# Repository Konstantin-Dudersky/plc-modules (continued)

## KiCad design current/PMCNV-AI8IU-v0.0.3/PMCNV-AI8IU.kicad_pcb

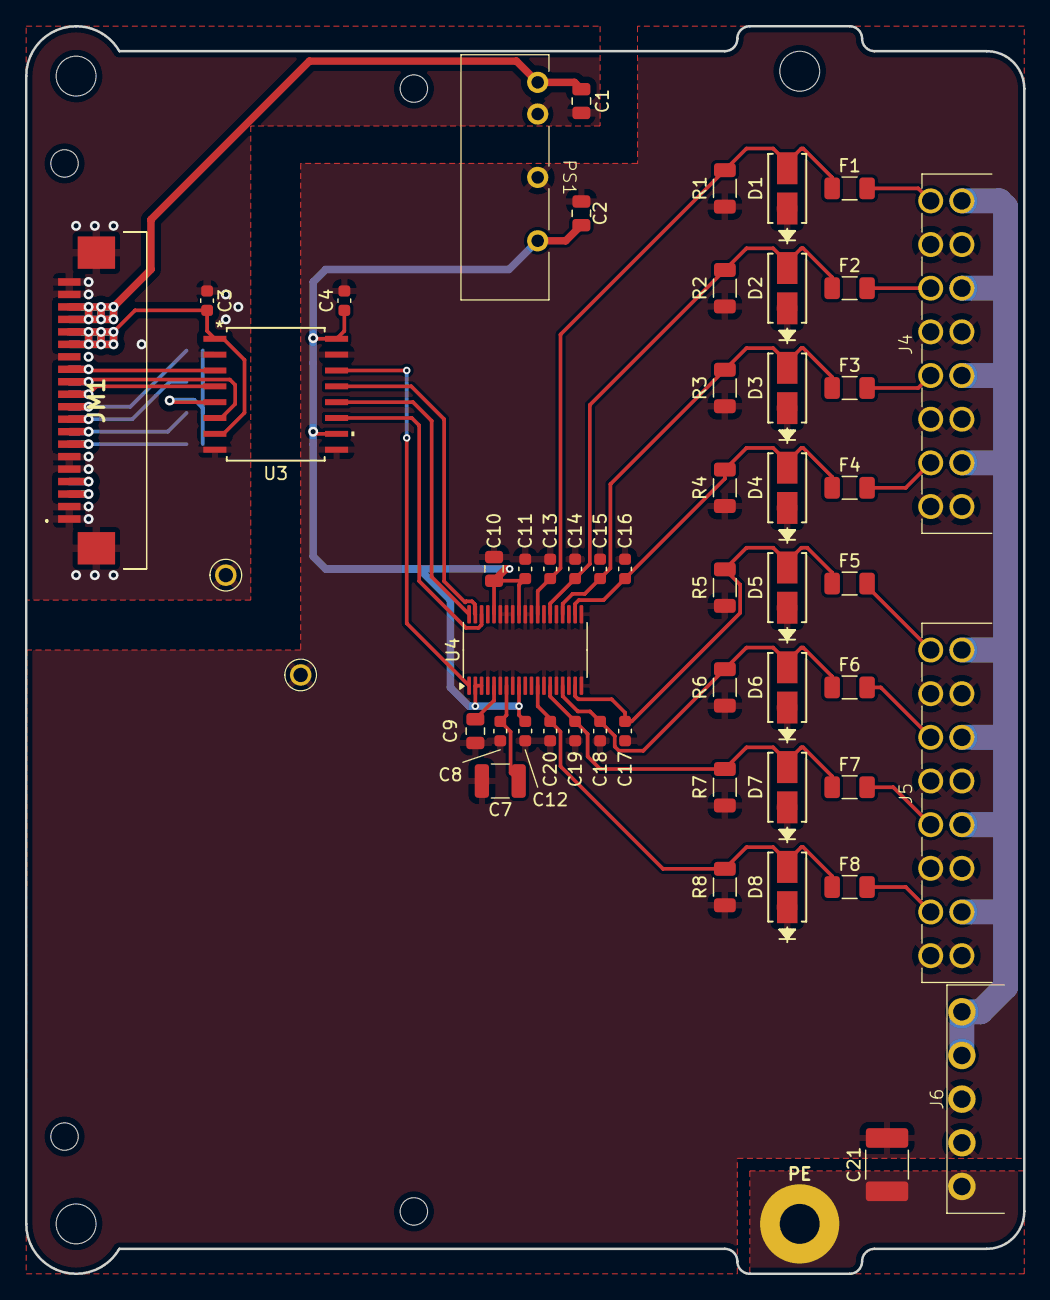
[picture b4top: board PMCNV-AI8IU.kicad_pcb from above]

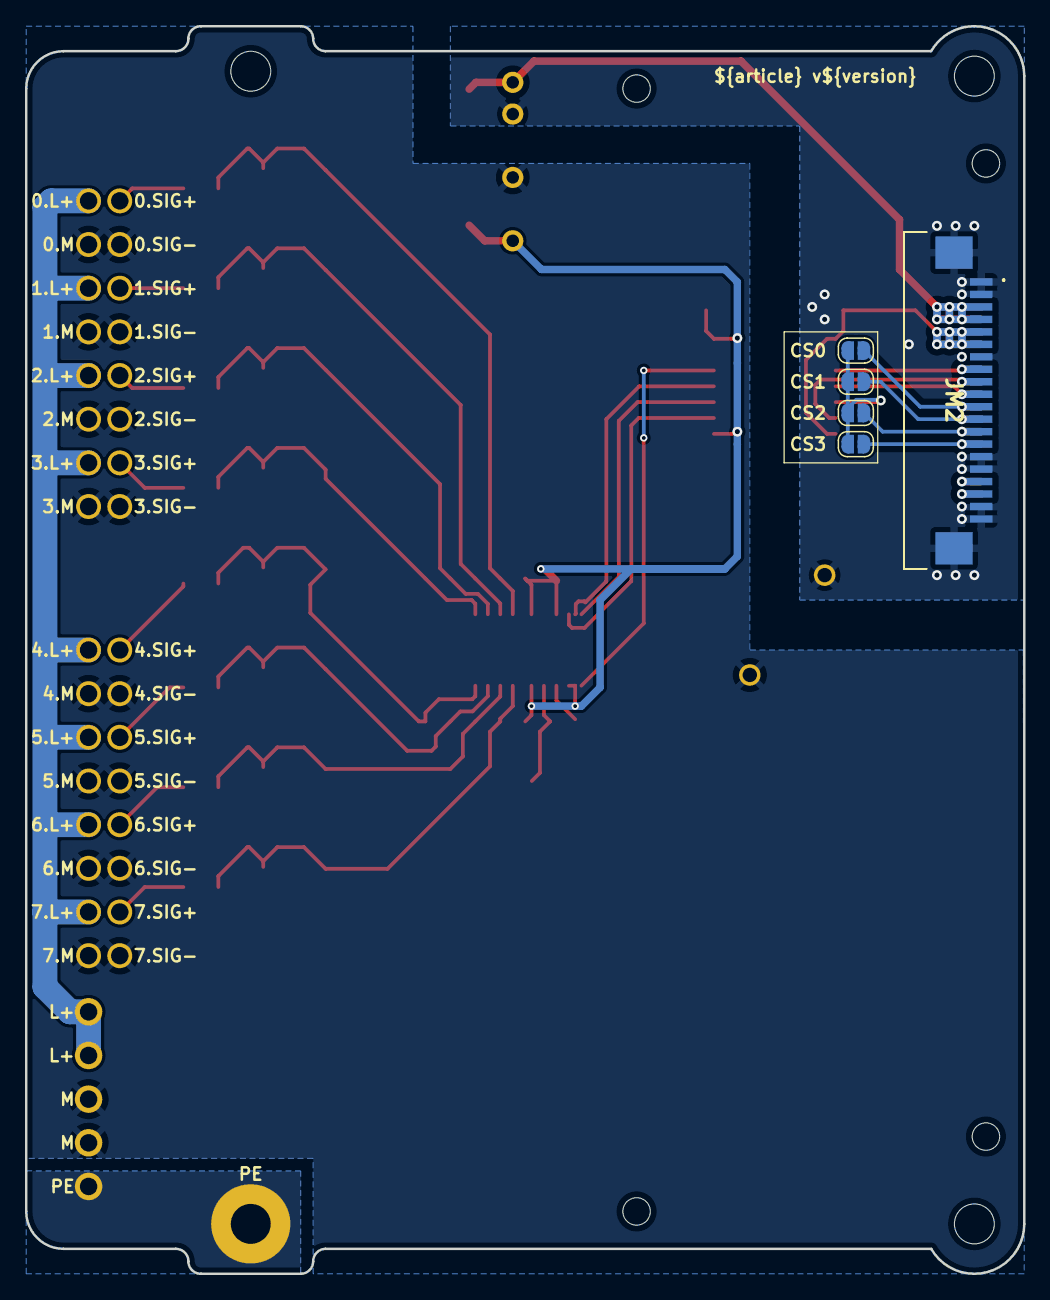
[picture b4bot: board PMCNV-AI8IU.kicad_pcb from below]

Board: 2 copper layers, 80.0 x 100.0 mm, 62 parts (5 on the bottom side), 39 nets.

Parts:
C1: 4.7uF; C_0805_2012Metric
C2, C9, C10: 10uF; C_0805_2012Metric
C3, C4: 100nF; C_0603_1608Metric
C7: 22uF; C_1210_3225Metric
C8, C11, C12: 1uF; C_0603_1608Metric
C13, C14, C15, C16, C17, C18, C19, C20: 10nF; C_0603_1608Metric
C21: 4.7nF 2kV; C_1812_4532Metric_Pad1.57x3.40mm_HandSolder
D1, D2, D3, D4, D5, D6, D7, D8: SMAJ33CA; SMASeries_LTF-M
D9: PE
F1, F2, F3, F4, F5, F6, F7, F8: nSMD005; Fuse_1206_3216Metric
H1, H2, H3: MountingHole; MountingHole_M3
J4, J5: 15EDGRHC-THR-3.5-16P
J6: 15EDGRC-3.5-05P
JM1, JM2: AFA07-S20FCC-00; AFA07S20FCA00
JP1, JP2, JP3, JP4: SolderJumper_2_Open; SolderJumper-2_P1.3mm_Open_RoundedPad1.0x1.5mm
PS1: 5V/5V; B2405LS-1WR3
R1, R2, R3, R4, R5, R6, R7, R8: 249R; R_1206_3216Metric
U1: PM-ESP32C3_v0.0.5
U2, U5: 5117
U3: CA-IS3741HW; SOIC16-WBW_CLG-M
U4: ADS8688; TSSOP-38_4.4x9.7mm_P0.5mm

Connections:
+3.3V_MCU: C3.2, JM1.15 (Pin_11), JM1.16 (Pin_11), JM2.5, JM2.6, U3.1 (VDD), U3.7 (ENA)
+5V_CNV: C2.1, C4.1, C10.2, C11.1, C12.1, PS1.6 (+V), U3.10 (ENB), U3.16 (VISO), U4.2 (~RST/PD), U4.3 (DAISY), U4.9 (AVDD), U4.30 (AVDD), U4.34 (DVDD)
+5V_MCU: C1.1, JM1.17 (Pin_11), JM1.18 (Pin_11), JM2.3, JM2.4, PS1.1 (Vin)
+24V_CNV: J4.10 (Pin_4), J4.12 (Pin_8), J4.14 (Pin_10), J4.16 (Pin_10), J5.10 (Pin_4), J5.12 (Pin_8), J5.14 (Pin_10), J5.16 (Pin_10), J6.4, J6.5
/0.SIG+: F1.2, J4.8 (Pin_9)
/1.SIG+: F2.2, J4.6 (Pin_9)
/2.SIG+: F3.2, J4.4
/3.SIG+: F4.2, J4.2 (Pin_3)
/4.SIG+: F5.2, J5.8 (Pin_9)
/5.SIG+: F6.2, J5.6 (Pin_9)
/6.SIG+: F7.2, J5.4
/7.SIG+: F8.2, J5.2 (Pin_3)
/AIN_0P: C18.1, D6.2 (A2), F6.1, R6.1, U4.16 (AIN_0P)
/AIN_1P: C17.1, D5.2 (A2), F5.1, R5.1, U4.18 (AIN_1P)
/AIN_2P: C16.1, D4.2 (A2), F4.1, R4.1, U4.21 (AIN_2P)
/AIN_3P: C15.1, D3.2 (A2), F3.1, R3.1, U4.23 (AIN_3P)
/AIN_4P: C14.1, D2.2 (A2), F2.1, R2.1, U4.25 (AIN_4P)
/AIN_5P: C13.1, D1.2 (A2), F1.1, R1.1, U4.27 (AIN_5P)
/AIN_6P: C20.1, D8.2 (A2), F8.1, R8.1, U4.12 (AIN_6P)
/AIN_7P: C19.1, D7.2 (A2), F7.1, R7.1, U4.14 (AIN_7P)
/CS0_MCU: JM1.10, JM2.11, JP1.1 (A)
/CS1_MCU: JM1.9, JM2.12 (Pin_11), JP2.1 (A)
/CS2_MCU: JM1.8, JM2.13 (Pin_11), JP3.1 (A)
/CS3_MCU: JM1.7, JM2.14 (Pin_11), JP4.1 (A)
/CS_CNV: U3.12 (VO3), U4.38 (~CS)
/CS_MCU: JP1.2 (B), JP2.2 (B), JP3.2 (B), JP4.2 (B), U3.5 (VI3)
/MISO_CNV: U3.11 (VI4), U4.36 (SDO)
/MISO_MCU: JM1.12 (Pin_11), JM2.9, U3.6 (VO4)
/MOSI_CNV: U3.14 (VO1), U4.1 (SDI)
/MOSI_MCU: JM1.13 (Pin_11), JM2.8, U3.3 (VI1)
/SCK_CNV: U3.13 (VO2), U4.37 (SCLK)
/SCK_MCU: JM1.11, JM2.10, U3.4 (VI2)
/SCL_MCU: JM1.3, JM2.18 (Pin_11)
/SDA_MCU: JM1.4, JM2.17 (Pin_11)
GND_CNV: C2.2, C4.2, C7.2, C8.2, C9.2, C10.1, C11.2, C12.2, C13.2, C14.2, C15.2, C16.2, C17.2, C18.2, C19.2, C20.2, C21.2, D1.1 (A1), D2.1 (A1), D3.1 (A1), D4.1 (A1), D5.1 (A1), D6.1 (A1), D7.1 (A1), D8.1 (A1), J4.1, J4.3, J4.5 (Pin_9), J4.7 (Pin_9), J4.9 (Pin_2), J4.11 (Pin_6), J4.13 (Pin_10), J4.15 (Pin_10), J5.1, J5.3, J5.5 (Pin_9), J5.7 (Pin_9), J5.9 (Pin_2), J5.11 (Pin_6), J5.13 (Pin_10), J5.15 (Pin_10), J6.2, J6.3, PS1.4 (0V), R1.2, R2.2, R3.2, R4.2, R5.2, R6.2, R7.2, R8.2, U3.9 (GNDB), U3.15 (GNDB), U4.4 (~REFSEL), U4.6 (REFGND), U4.8 (AGND), U4.13 (AIN_6GND), U4.15 (AIN_7GND), U4.17 (AIN_0GND), U4.19 (AIN_1GND), U4.20 (AIN_2GND), U4.22 (AIN_3GND), U4.24 (AIN_4GND), U4.26 (AIN_5GND), U4.28 (AGND), U4.29 (AGND), U4.31 (AGND), U4.32 (AGND), U4.33 (DGND), U5.1
GND_MCU: C1.2, C3.1, JM1.1, JM1.2, JM1.5, JM1.6, JM1.14 (Pin_11), JM1.19 (Pin_11), JM1.20 (Pin_11), JM1.MP1 (Pin_11), JM1.MP2 (Pin_11), JM2.1, JM2.2, JM2.7, JM2.15 (Pin_11), JM2.16 (Pin_11), JM2.19 (Pin_11), JM2.20 (Pin_11), JM2.MP1 (Pin_11), JM2.MP2 (Pin_11), PS1.2 (GND), U2.1, U3.2 (GNDA), U3.8 (GNDA)
unnamed: C7.1, C8.1, U4.7 (REFCAP)
unnamed: C9.1, U4.5 (REFIO)
PE: C21.1, D9.1, J6.1

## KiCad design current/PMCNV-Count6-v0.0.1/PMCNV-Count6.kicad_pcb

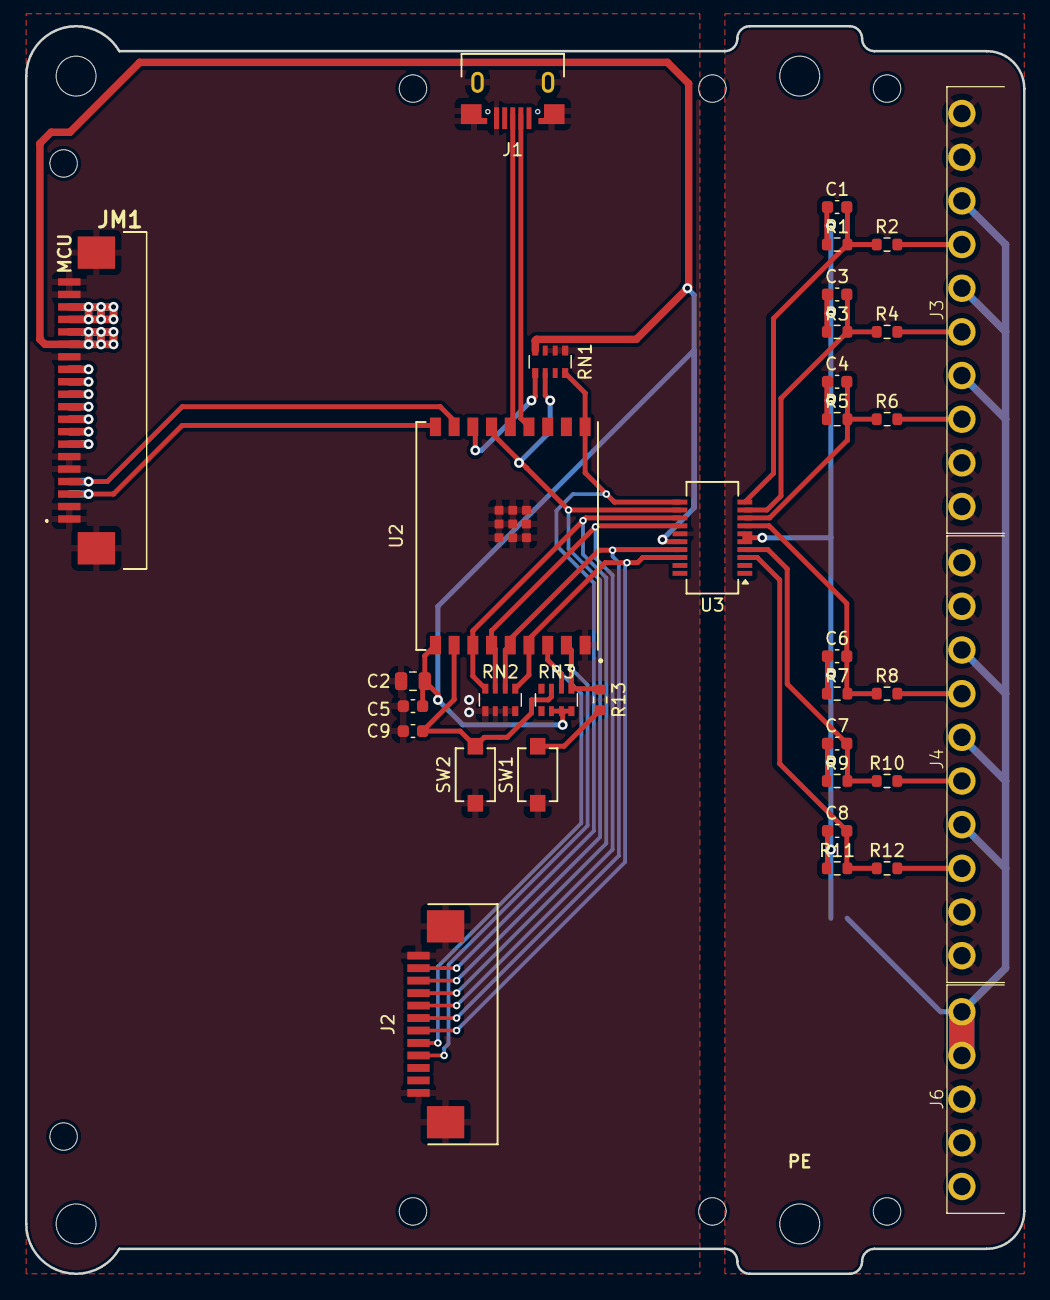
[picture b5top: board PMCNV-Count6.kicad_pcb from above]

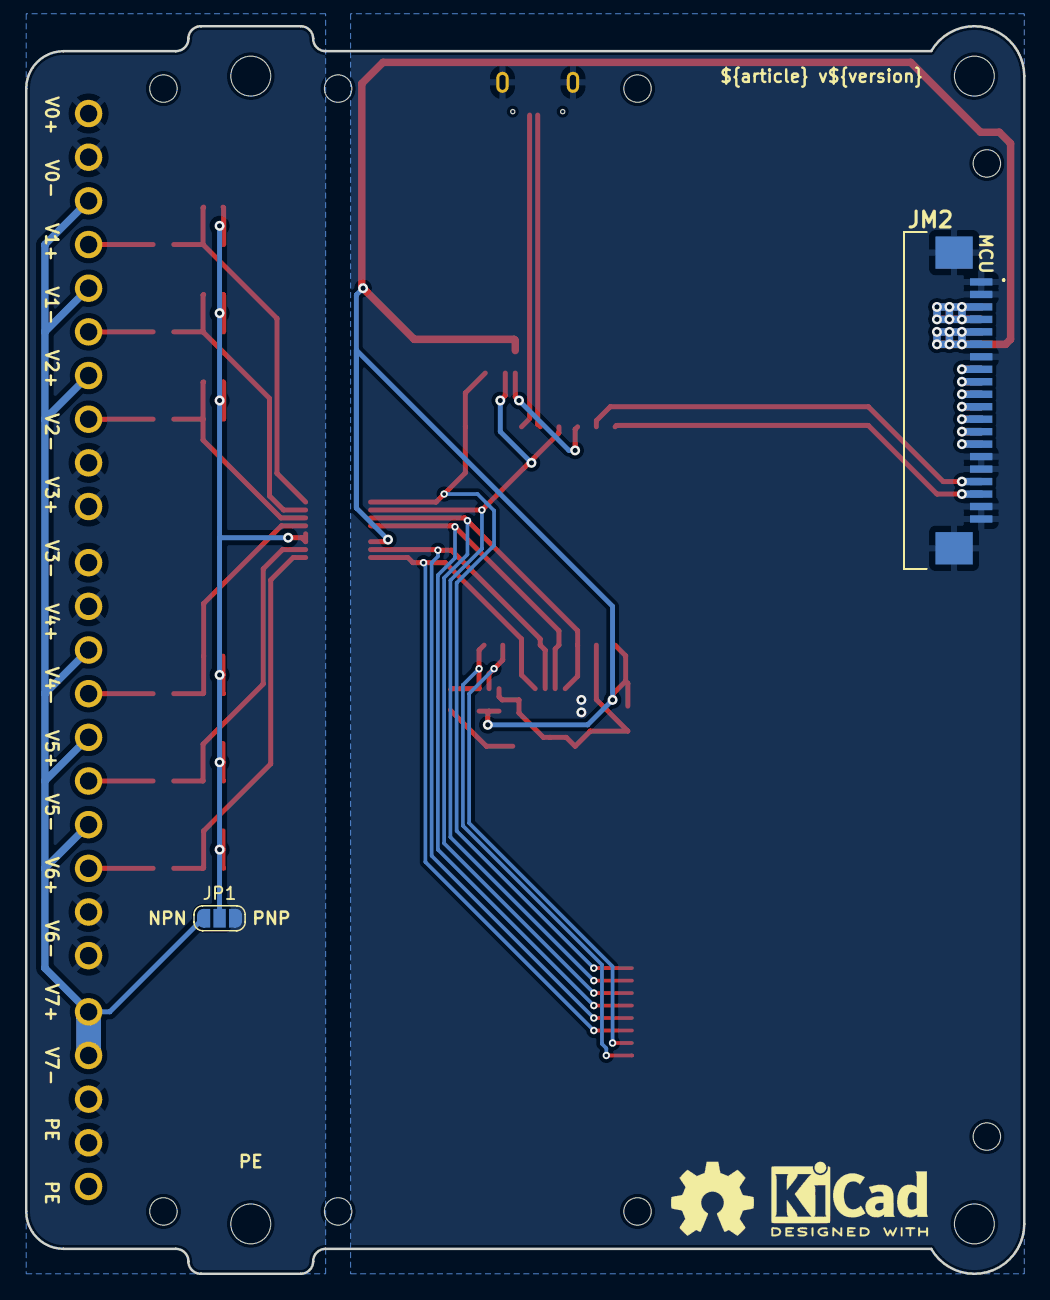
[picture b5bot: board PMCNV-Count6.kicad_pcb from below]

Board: 2 copper layers, 80.0 x 100.0 mm, 45 parts (4 on the bottom side), 40 nets.

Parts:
C1, C3, C4, C6, C7, C8: 2.2nF; C_0603_1608Metric
C2: 10uF; C_0805_2012Metric
C5, C9: 1uF; C_0603_1608Metric
H4, H5, H6, H7: MountingHole_M3
J1: U254-051T-4BH83-S1S; CONN5_H83-S1S_XKB
J2: AFA07-S12FCC-00; CONN10_AFA07-S12_JUS
J3, J4: 15EDGRC-3.5-10P
J6: 15EDGRC-3.5-05P
JM1, JM2: AFA07-S20FCC-00; AFA07S20FCA00
JP1: SolderJumper_3_Open; SolderJumper-3_P1.3mm_Open_RoundedPad1.0x1.5mm
R1, R3, R5, R7, R9, R11: 750R; R_0603_1608Metric
R2, R4, R6, R8, R10, R12: 2k7; R_0603_1608Metric
R13: 330R; R_0603_1608Metric
RN1, RN2, RN3: 10k; R_Array_Convex_4x0603
SP1: PM_LED-xx-v0.0.1
SW1, SW2: Button; SW_TS-1088_XNP-M
U1: PM-ESP32C3_v0.0.5
U2: ESP32-C3-WROOM-02U-N4; ESP32-C3-WROOM-02U_EXP
U3: CA-IS3988P; SSOP-20_3.9x8.7mm_P0.635mm
kicad_logo: KiCad-Logo2_5mm_SilkScreen
oshw_logo: OSHW-Symbol_6.7x6mm_SilkScreen

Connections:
+3.3V_MCU: C2.1, C5.1, JM1.15 (Pin_11), JM1.16 (Pin_11), JM2.5, JM2.6, RN1.4 (R4.1), RN3.6 (R3.2), RN3.7 (R2.2), RN3.8 (R1.2), U2.1 (3V3), U3.16 (VDD)
+5V_MCU: JM1.17 (Pin_11), JM1.18 (Pin_11), JM2.3, JM2.4
/COM_CNV: C1.1, C3.1, C4.1, C6.1, C7.1, C8.1, JP1.2 (C), R1.1, R3.1, R5.1, R7.1, R9.1, R11.1, U3.5 (COM), U3.6 (COM)
/CS0_MCU: JM1.10, JM2.11
/CS1_MCU: JM1.9, JM2.12 (Pin_11)
/CS2_MCU: JM1.8, JM2.13 (Pin_11)
/CS3_MCU: JM1.7, JM2.14 (Pin_11)
/EN: C9.1, RN3.3 (R3.1), SW2.2, U2.2 (EN)
/LED0: J2.5, RN3.2 (R2.1), U2.7 (IO8)
/LED1: J2.4, R13.2, RN3.1 (R1.1), U2.8 (IO9)
/MISO_MCU: JM1.12 (Pin_11), JM2.9
/MOSI_MCU: JM1.13 (Pin_11), JM2.8
/SCK_MCU: JM1.11, JM2.10
/SCL_MCU: JM1.3, JM2.18 (Pin_11), U2.18 (IO0)
/SDA_MCU: JM1.4, JM2.17 (Pin_11), U2.17 (IO1)
/USB_D+: J1.3 (D+), U2.14 (IO19_(USB_D+))
/USB_D-: J1.2 (D-), U2.13 (IO18_(USB_D-))
/a.0: J2.11, RN1.8 (R1.2), U2.10 (IO10), U3.11 (BH8)
/a.0_div: C1.2, R1.2, R2.1, U3.10 (AH8)
/a.0_in: J3.7, R2.2
/a.1: J2.10, RN1.6 (R3.2), U2.15 (IO3), U3.12 (BH7)
/a.1_div: C3.2, R3.2, R4.1, U3.9 (AH7)
/a.1_in: J3.5, R4.2
/a.2: J2.9, RN2.8 (R1.2), U2.3 (IO4), U3.13 (BH6)
/a.2_div: C4.2, R5.2, R6.1, U3.8 (AH6)
/a.2_in: J3.3, R6.2
/a.3: J2.8, RN2.7 (R2.2), U2.4 (IO5), U3.14 (BH5)
/a.3_div: C6.2, R7.2, R8.1, U3.7 (AH5)
/a.3_in: J4.7, R8.2
/a.4: J2.7, RN2.6 (R3.2), U2.5 (IO6), U3.17 (BH4)
/a.4_div: C7.2, R9.2, R10.1, U3.4 (AH4)
/a.4_in: J4.5, R10.2
/a.5: J2.6, RN2.5 (R4.2), U2.6 (IO7), U3.18 (BH3)
/a.5_div: C8.2, R11.2, R12.1, U3.3 (AH3)
/a.5_in: J4.3, R12.2
GND_CNV: J3.1, J3.2, J3.9, J3.10, J4.1, J4.2, J4.9, J4.10, J6.2, J6.3, JP1.1 (A)
GND_MCU: C2.2, C5.2, C9.2, J1.5 (GND), J2.1, J2.12 (Pin_11), J2.13 (Pin_11), JM1.1, JM1.2, JM1.5, JM1.6, JM1.14 (Pin_11), JM1.19 (Pin_11), JM1.20 (Pin_11), JM1.MP1 (Pin_11), JM1.MP2 (Pin_11), JM2.1, JM2.2, JM2.7, JM2.15 (Pin_11), JM2.16 (Pin_11), JM2.19 (Pin_11), JM2.20 (Pin_11), JM2.MP1 (Pin_11), JM2.MP2 (Pin_11), RN1.1 (R1.1), RN1.2 (R2.1), RN1.3 (R3.1), RN2.1 (R1.1), RN2.2 (R2.1), RN2.3 (R3.1), RN2.4 (R4.1), SW1.1, SW2.1, U2.9 (GND), U2.EPAD, U3.15 (GND)
L+_CNV: J3.4, J3.6, J3.8, J4.4, J4.6, J4.8, J6.4, J6.5, JP1.3 (B)
unnamed: R13.1, SW1.2
unnamed: RN1.5 (R4.2), U2.16 (IO2)

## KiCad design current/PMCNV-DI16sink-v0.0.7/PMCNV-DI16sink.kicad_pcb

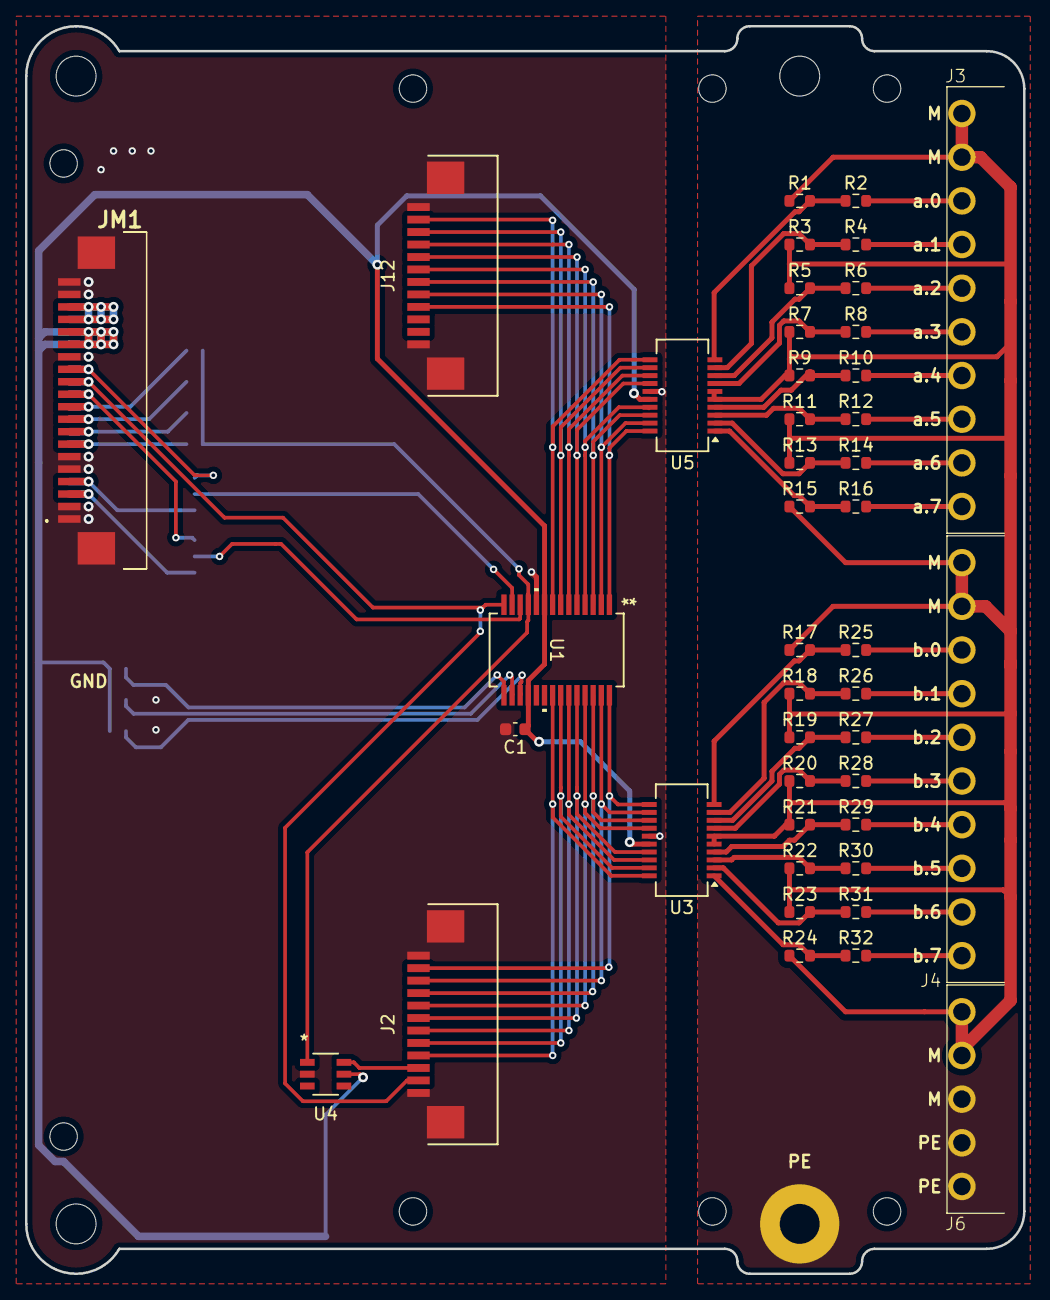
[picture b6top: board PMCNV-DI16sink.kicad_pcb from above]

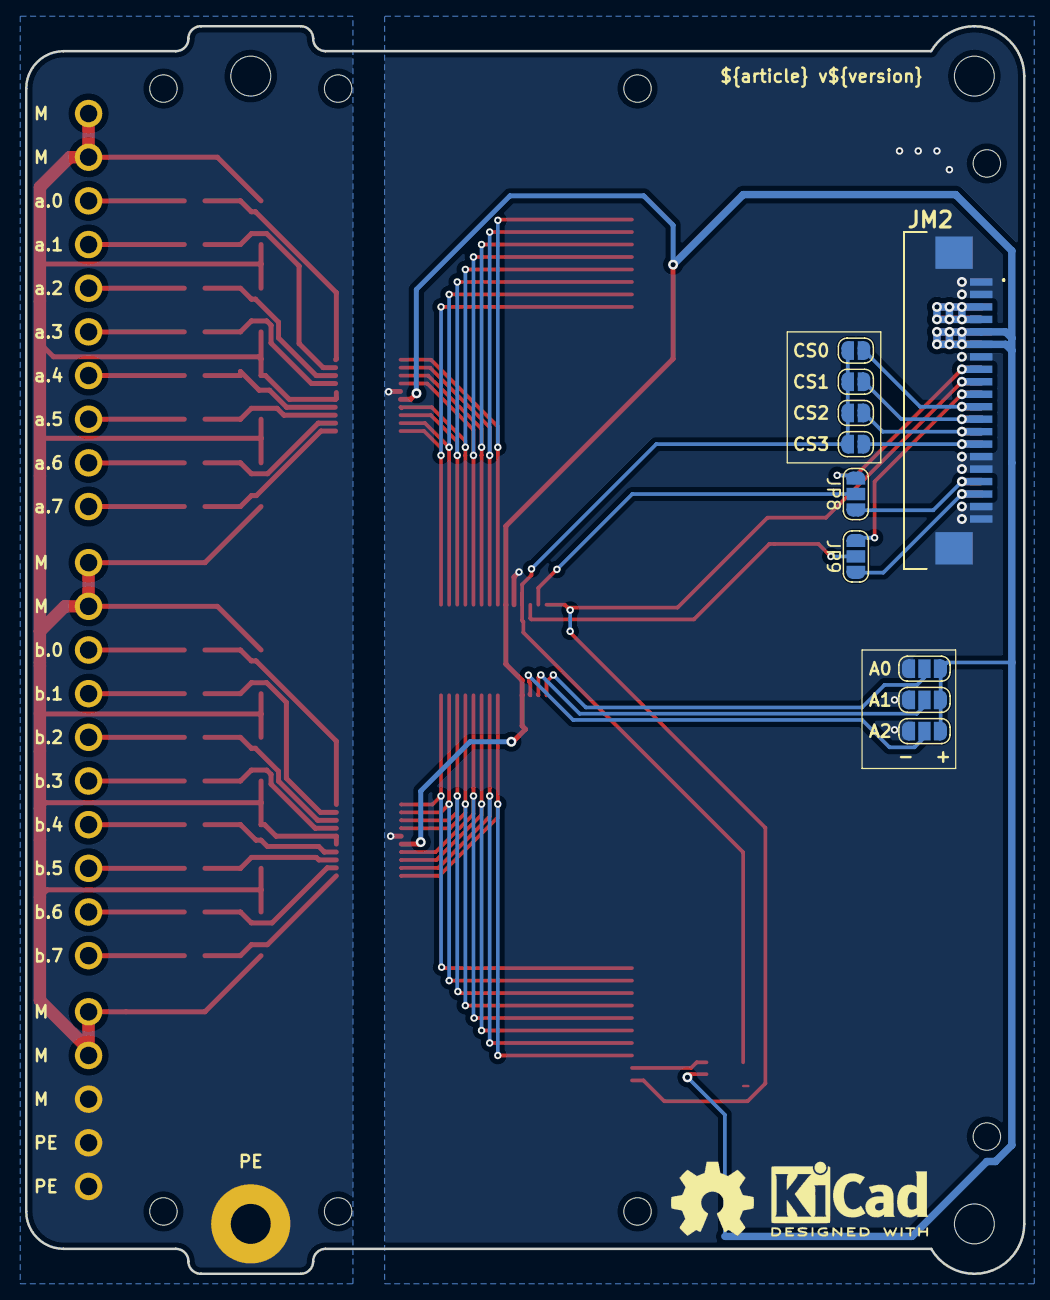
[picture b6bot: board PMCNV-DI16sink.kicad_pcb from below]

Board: 2 copper layers, 80.0 x 100.0 mm, 61 parts (12 on the bottom side), 69 nets.

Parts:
C1: 100nF; C_0603_1608Metric
H4, H5, H6: MountingHole_M3
J2, J12: AFA07-S12FCC-00; CONN10_AFA07-S12_JUS
J3, J4: 15EDGRC-3.5-10P
J6: 15EDGRC-3.5-05P
JM1, JM2: AFA07-S20FCC-00; AFA07S20FCA00
JP1, JP2, JP3, JP4: SolderJumper_2_Open; SolderJumper-2_P1.3mm_Open_RoundedPad1.0x1.5mm
JP5, JP6, JP7, JP8, JP9: SolderJumper_3_Open; SolderJumper-3_P1.3mm_Open_RoundedPad1.0x1.5mm
PE1: PE
R1, R3, R5, R7, R9, R11, R13, R15, R17, R18, R19, R20, R21, R22, R23, R24: 750R; R_0603_1608Metric
R2, R4, R6, R8, R10, R12, R14, R16, R25, R26, R27, R28, R29, R30, R31, R32: 2k7; R_0603_1608Metric
SP1: PM_LED-xx-v0.0.1
U1: MCP23S17_SS; SSOP28_MC_MCH
U2: PM-ESP32C3_v0.0.5
U3, U5: CA-IS3980P; SSOP-20_3.9x8.7mm_P0.635mm
U4: SN74LVC2G14DBVR; DBV6-M
kicad_logo: KiCad-Logo2_5mm_SilkScreen
oshw_logo: OSHW-Symbol_6.7x6mm_SilkScreen

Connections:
+3.3V_MCU: C1.1, JM1.15 (Pin_11), JM1.16 (Pin_11), JM2.5, JM2.6, JP5.3 (B), JP6.3 (B), JP7.3 (B), U1.9 (VDD), U1.18 (~RESET), U3.16 (VDD), U4.5 (VCC), U5.16 (VDD)
+5V_MCU: JM1.17 (Pin_11), JM1.18 (Pin_11), JM2.3, JM2.4
/A0: JP5.2 (C), U1.15 (A0)
/A1: JP6.2 (C), U1.16 (A1)
/A2: JP7.2 (C), U1.17 (A2)
/CS0_MCU: JM1.10, JM2.11, JP1.1 (A)
/CS1_MCU: JM1.9, JM2.12 (Pin_11), JP2.1 (A)
/CS2_MCU: JM1.8, JM2.13 (Pin_11), JP3.1 (A)
/CS3_MCU: JM1.7, JM2.14 (Pin_11), JP4.1 (A)
/CS_LED: J2.3, U4.6 (1Y)
/CS_MCU: JP1.2 (B), JP2.2 (B), JP3.2 (B), JP4.2 (B), U1.11 (~CS), U4.1 (1A)
/GND_CNV: J3.9, J3.10, J4.9, J4.10, J6.4, J6.5, R1.1, R3.1, R5.1, R7.1, R9.1, R11.1, R13.1, R15.1, R17.1, R18.1, R19.1, R20.1, R21.1, R22.1, R23.1, R24.1, U3.5 (COM), U3.6 (COM), U5.5 (COM), U5.6 (COM)
/MISO_MCU: J2.2, JM1.12 (Pin_11), JM2.9, U1.14 (SO)
/MOSI_MCU: JM1.13 (Pin_11), JM2.8, JP8.3 (B)
/PE: J6.1, J6.2, J6.3, PE1.1
/SCK_MCU: JM1.11, JM2.10, JP9.3 (B)
/SCL_MCU: JM1.3, JM2.18 (Pin_11), JP9.1 (A)
/SDA_MCU: JM1.4, JM2.17 (Pin_11), JP8.1 (A)
/a.0: J12.11, U1.8 (GPB7), U5.11 (B8)
/a.0_div: R1.2, R2.1, U5.10 (A8)
/a.0_in: J3.8, R2.2
/a.1: J12.10, U1.7 (GPB6), U5.12 (B7)
/a.1_div: R3.2, R4.1, U5.9 (A7)
/a.1_in: J3.7, R4.2
/a.2: J12.9, U1.6 (GPB5), U5.13 (B6)
/a.2_div: R5.2, R6.1, U5.8 (A6)
/a.2_in: J3.6, R6.2
/a.3: J12.8, U1.5 (GPB4), U5.14 (B5)
/a.3_div: R7.2, R8.1, U5.7 (A5)
/a.3_in: J3.5, R8.2
/a.4: J12.7, U1.4 (GPB3), U5.17 (B4)
/a.4_div: R9.2, R10.1, U5.4 (A4)
/a.4_in: J3.4, R10.2
/a.5: J12.6, U1.3 (GPB2), U5.18 (B3)
/a.5_div: R11.2, R12.1, U5.3 (A3)
/a.5_in: J3.3, R12.2
/a.6: J12.5, U1.2 (GPB1), U5.19 (B2)
/a.6_div: R13.2, R14.1, U5.2 (A2)
/a.6_in: J3.2, R14.2
/a.7: J12.4, U1.1 (GPB0), U5.20 (B1)
/a.7_div: R15.2, R16.1, U5.1 (A1)
/a.7_in: J3.1, R16.2
/b.0: J2.11, U1.28 (GPA7), U3.11 (B8)
/b.0_div: R17.2, R25.1, U3.10 (A8)
/b.0_in: J4.8, R25.2
/b.1: J2.10, U1.27 (GPA6), U3.12 (B7)
/b.1_div: R18.2, R26.1, U3.9 (A7)
/b.1_in: J4.7, R26.2
/b.2: J2.9, U1.26 (GPA5), U3.13 (B6)
/b.2_div: R19.2, R27.1, U3.8 (A6)
/b.2_in: J4.6, R27.2
/b.3: J2.8, U1.25 (GPA4), U3.14 (B5)
/b.3_div: R20.2, R28.1, U3.7 (A5)
/b.3_in: J4.5, R28.2
/b.4: J2.7, U1.24 (GPA3), U3.17 (B4)
/b.4_div: R21.2, R29.1, U3.4 (A4)
/b.4_in: J4.4, R29.2
/b.5: J2.6, U1.23 (GPA2), U3.18 (B3)
/b.5_div: R22.2, R30.1, U3.3 (A3)
/b.5_in: J4.3, R30.2
/b.6: J2.5, U1.22 (GPA1), U3.19 (B2)
/b.6_div: R23.2, R31.1, U3.2 (A2)
/b.6_in: J4.2, R31.2
/b.7: J2.4, U1.21 (GPA0), U3.20 (B1)
/b.7_div: R24.2, R32.1, U3.1 (A1)
/b.7_in: J4.1, R32.2
GND_MCU: C1.2, J2.1, J2.12 (Pin_11), J2.13 (Pin_11), J12.1, J12.12 (Pin_11), J12.13 (Pin_11), JM1.1, JM1.2, JM1.5, JM1.6, JM1.14 (Pin_11), JM1.19 (Pin_11), JM1.20 (Pin_11), JM1.MP1 (Pin_11), JM1.MP2 (Pin_11), JM2.1, JM2.2, JM2.7, JM2.15 (Pin_11), JM2.16 (Pin_11), JM2.19 (Pin_11), JM2.20 (Pin_11), JM2.MP1 (Pin_11), JM2.MP2 (Pin_11), JP5.1 (A), JP6.1 (A), JP7.1 (A), U1.10 (VSS), U3.15 (GND), U4.2 (GND), U5.15 (GND)
unnamed: JP8.2 (C), U1.13 (SI)
unnamed: JP9.2 (C), U1.12 (SCK)
